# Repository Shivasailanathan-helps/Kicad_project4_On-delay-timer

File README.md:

# Kicad_project4_On-delay-timer
This Project gives a On-Delay Timer 2 layer PCB in KiCad using an NE555 timer in monostable mode to process low-voltage DC signals and create a designated time delay. The circuit uses a transistor to safely drive an relay for switching high-power AC/DC loads, protected by a flyback diode against spikes, with LED for visual timing status.

### Features:
Timing & Logic Architecture: NE555 timer IC configured in monostable multivibrator mode, utilizing an RC network (R1, C1) to generate precise on-delay pulse timing.
Transistor Driver & Inductive Protection: NPN transistor (BC547) low-side switch for relay coil actuation, paired with a anti-parallel flyback diode (D2) across the coil to clamp inductive back-EMF voltage spikes (V = L*(di/dt)).

Galvanic Load Switching: Onboard SPDT relay (K1) coupled to a 3-pin high-voltage screw terminal block (J2: NC, C, NO) for total electrical isolation between control circuitry and external AC/DC loads.

Visual Status Indication: Through-Hole (THT) 5mm dome LED (D1) with a 330ohm resistor with series current-limiting resistor (R2) for clear, wide-angle visual timing status.
Dual-Layer Copper Pour Strategy: Continuous Bottom Copper (B.Cu) Ground (GND) plane for low-impedance current return paths and noise immunity, alongside a Top Copper (F.Cu) +5V power zone for low-resistance power distribution.Enclosure-Ready Mechanical Layout: Four corner M3 mounting holes with copper/via keepouts and smooth rounded corner radii via PCB edge fillets.

### Process:
Phase 1: Schematic Capture, Footprints & Draft BOM
Schematic & Netlist Setup: Captured the NE555 monostable circuit, transistor switch, protection diode, and terminal blocks, verifying pin connections and running Electrical Rules Check (ERC).

IPC-7351 Footprint Assignment: Assigned standardized footprints across all components (SOIC-8 for U1, TO-92 for Q1, LED_THT:LED_D5.0mm for D1, standard SMD passive packages for resistors/capacitors, and heavy-duty THT footprints for K1/J2).

Phase 2: PCB Layout & Physical RoutingNetlist Transfer & Placement: 
Pushed schematic data to PCB Editor (F8). Rotated (R) and positioned components (R1–R4, U1, Q1) to untangle ratsnest lines—placing timing components directly adjacent to U1 pins 2 (TRIG) and 7 (DISCH).

Edge Geometry & Fillets: Defined the PCB boundary on the Edge.Cuts layer and applied the Fillet Lines tool (Shape Modification -> Fillet Lines) to convert sharp 90 degree corners into smooth rounded edges. 

Trace Routing & Zone Fills: Routed all signal and power connections with 45 degree trace bends. Flooded B.Cu with a GND zone and F.Cu with a +5V zone, pressing B to calculate zone fills.

### Extras:
Why Use a Transistor Driver (BC547) and Flyback Diode (D_2) for the Relay?
Relay Coil Drive: Driving a relay coil directly from the 555 output can cause current loading and thermal stress on the IC. The BC547 acts as an efficient low-side switch to turn the coil on and off reliably. 

Inductive Spike Clamping: When the relay turns off, the magnetic field in the coil collapses instantly, generating a massive reverse voltage spike. The flyback diode (D2) provides a safe recirculating path for this energy, protecting Q1 and U1 from high-voltage breakdown.

### Design Problems Encountered & Practical Rectifications
During the design and layout of the NE555-based On-Delay Timer module, several electrical, layout, and software verification challenges were identified and systematically resolved.

1. Component Reference Designator Mismatch (R1 vs R3)
Problem: Visual layout discrepancy between your schematic design and the instructor's reference PCB, where R1 and R3 appeared swapped.
Theory: KiCad routes based on Netlist continuity, not visual refdes strings. The netlist tracks electrical nodes regardless of component labels.
Rectification: Verified ratsnest connection paths in the PCB Editor (R3 Pad 2 connected to U1 Pin 2 TRIG; R1 Pad 2 connected to Pin 7 DISCH). Rotated (R) and repositioned the footprints to align with netlist paths without breaking electrical logic.

2. Hidden Copper Traces in 3D Viewer Render
Problem: Copper tracks rendered clearly in earlier projects appeared "missing" or blended into the board surface in 3D mode.
Theory: Adding a continuous Bottom Copper Ground Pour (B.Cu) floods copper across the entire layer. When covered by green solder mask epoxy, routed traces and ground fills merge into a uniform surface.
Rectification: Verified trace geometries by turning off the front solder mask (F.Mask) in the 3D Viewer Appearance Panel and pressing B in the PCB editor to recalculate zone fills.

3. Thermal Relief Spoke Count DRC Violation (R3 Pad 1)
Problem: DRC flagged Error: Thermal relief connection to zone in... F.Cu; zone min spoke count 2; actual 1 at Pad 1 of R3.
Theory: Heavy copper pours absorb heat rapidly during soldering. Thermal relief spokes restrict heat flow to prevent cold solder joints. If surrounding signal traces crowd a pad, KiCad cannot route the default minimum of 2 copper spokes.
Rectification: Manually routed a direct 45 degree copper trace (X) from R3 Pad 1 to the main +5V rail and nudged adjacent traces (D) to grant the zone space for a second spoke.

4. Unconnected Net and Silkscreen Clearance Warnings
Problem: DRC reported 1 unconnected net between J1 Pin 1 (+5V) and R1/R3, alongside 3 silkscreen clearance warnings (J2, R1, R2 text touching footprint boundary lines).
Theory: Overlapping silkscreen ink over solder pads or outer mechanical boundaries causes ink flaking during assembly and violates fab clearance rules.
Rectification: Completed the missing +5V trace route and used the move command (M) to position all reference designator text clearly outside component outlines (K1 relay box and J1 connector outline).

5. SMD to THT LED Package Conversion
Problem: Upgraded output status indicator from an SMD 0805 LED to a Through-Hole (THT) 5mm LED.
Theory: SMD LEDs emit light planar to the PCB surface. A THT 5mm dome LED focuses light forward, making it visible through enclosure cutouts.
Rectification: Reassigned the schematic symbol footprint to LED_THT:LED_D5.0mm while keeping the electrical current-limiting network identical (R2 = 330ohms).

### Outputs:

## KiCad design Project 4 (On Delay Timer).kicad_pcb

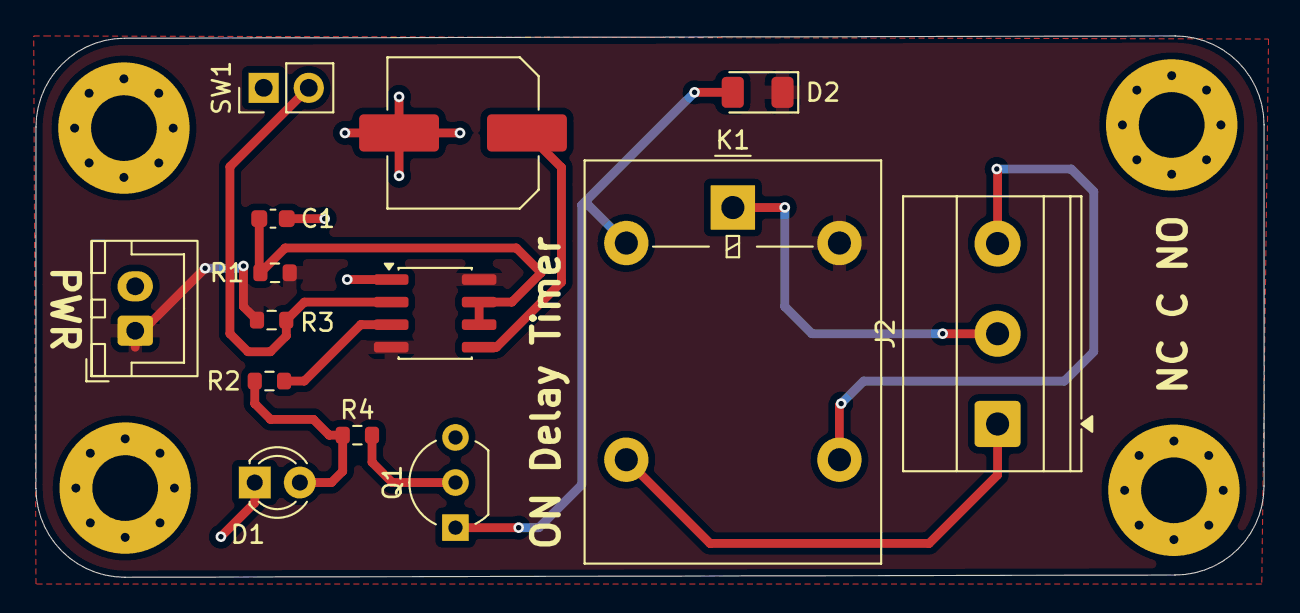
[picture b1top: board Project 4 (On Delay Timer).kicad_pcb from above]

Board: 2 copper layers, 69.2 x 30.5 mm, 18 parts (0 on the bottom side), 12 nets.

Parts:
C1: 10uF/16V; C_0603_1608Metric
C2: 0.01uF; C_Elec_8x10.2
D1: LED; LED_D3.0mm_Clear
D2: D_Small; D_1206_3216Metric
H1, H2, H3, H4: MountingHole_3.7mm_Pad_Via
J1: Pins; JST_XH_B2B-XH-A_1x02_P2.50mm_Vertical
J2: AC Connector; TerminalBlock_Phoenix_MKDS-1,5-3-5.08_1x03_P5.08mm_Horizont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
K1: G5LE-1; Relay_SPDT_Omron-G5LE-1
Q1: BC547; TO-92_Inline_Wide
R1: 100K; R_0603_1608Metric
R2, R4: 330E; R_0603_1608Metric
R3: 10K; R_0603_1608Metric
SW1: SW_Push; PinHeader_1x02_P2.54mm_Vertical
U1: NE555D; SOIC-8_3.9x4.9mm_P1.27mm

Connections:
+5V: D2.1 (K), J1.1, K1.5, R1.1, R3.1, U1.4 (~RST), U1.8 (VCC)
GND: C1.2, C2.2, D1.1 (K), H1.1 (1_1), H2.1 (1_1), H3.1 (1_1), H4.1 (1_1), J1.2, Q1.3 (E), SW1.1, U1.1 (GND)
unnamed: D1.2 (A), R2.2, R4.1
unnamed: D2.2 (A), K1.2, Q1.1 (C)
unnamed: J2.1, K1.3
unnamed: J2.2, K1.1
unnamed: J2.3, K1.4
unnamed: Q1.2 (B), R4.2
unnamed: C2.1, U1.5 (CONT)
unnamed: C1.1, R1.2, U1.6 (THRES), U1.7 (DISCH)
unnamed: R2.1, U1.3 (OUT)
unnamed: R3.2, SW1.2, U1.2 (TRIG)
